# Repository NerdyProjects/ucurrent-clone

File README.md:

### ucurrent clone

This repository holds a clone of the ucurrent gold from https://www.eevblog.com/projects/ucurrent/

### Design changes
* Reimplementation of design in kicad
* exchanged switches for jumpers to reduce cost
* changed shunt usage which reduces accuracy of some measurement regions for simplicity
* used cheaper resistors for a reduced total accuracy which should be good enough for most use cases

### Description of range selection
Range selection happens by putting a jumper on the selector panel.
To change the range without powering of the device under test, just use a second jumper and remove the first one later.
The proposed sense resistors are:
* 10 milli ohms, selected in the most bottom row. (1 mV / mA)
* 90 + 10 milli ohms, selected by the second row from bottom (10 mV / mA, allows more precise measurements in the typical 0-125/250 mA region)
* 10,1 ohms (1.01 mV / µA; so 1 mV/µA with +1% error), selected by the third row from bottom. The measurement error can be mostly removed by setting a second jumper vertically on the bottom right to bridge R5.
* 10010,1 ohms (1.00101 mV / nA; so 1 mV/nA with + 0.1% error), selected by a vertical jumper on the top left)

### BOM changes
* Most precision resistors are available as 0.1% / 25ppm/K versions from the german distributor Reichelt.
* R5 has a special value of 90 mOhms and can be bridged if none can be obtained (or use a lower value).
* All shunt resistors are used as 1% versions. You are free to use more accurate ones to improve accuracy. I did rather safe 10 euros...
* The battery indication around the TPS3839 (compatible to TPS3809) is fully optional and activated by a push button. Device needs to be powered on!
* Power can be fed via an external source, power selection (external/battery/off) happens via jumper.

### BOM

| Count | Reference | Description | Purpose | Digikey | Reichelt | Price (total) |
| ---   | --------- | ----------- | ------- | ------- | -------- | ------------- |
| 1 | BT1 | CR2032 Battery Holder SMD | | 1060K-ND | | 1,05 € |
| 1 | - | Case 64x44x32mm | | | RND 455-00094 | 1,01 € |
| 2 | C1, C2 | Capacitor X7R 100 nF 0805 | blocking cap | | | 0,05 € |
| 2 | C3, C4 | Capacitor, 10 pF 0805 | opamp stabilization | | | 0,05 € |
| 2 | J2, J3, J6, J7 | Banana Jack 4mm red | measurement connections | | BIL 20 RT, BB 4 RT BD | 1,76 €, 0,64 € |
| 2 | J2, J3, J6, J7 | Banana Jack 4mm black | measurement connections | | BIL 20 SW, BB 4 SW BD | 1,76 €, 0,64 € | 
| 1 | J4 | jumper terminal, 1x03, 2,54mm | power selector | | | 0,05 € |
| 1 | J1 | jumper or screw terminal, 1x02, 2,54mm | external power | | | 0,20 € |
| 1 | J5 | double row connector, 02x04, 2,54mm | measurement range selection | | | 0,10 € |
| 4 | R1, R7, R10, R16 | Resistor 270 ohms 0805 (any) | | | | 0,05 € |
| 1 | R2 | Resistor 10 mOhms 1206 <= 1%, TC < 100 ppm | Shunt for 1mV/mA range | ERJ-6CWDR010V (0,5%, 75ppm)| | 0,75 € |
| 2 | R3, R4 | Resistor 100 kOhms 0805 (any) | voltage divider for VGND | | | 0,02 € |
| 1 | R5 | Resistor 90 mOhms 0805 <= 1%, TC < 100 ppm | Shunt for 10mV/mA range | WSL0805R0900FEA (1%, 75ppm) | | 0,85 € |
| 1 | R6 | Resistor 10 Ohms 0805 <= 1%, TC < 100 ppm | Shunt for 1mV/µA range | RR12Q10DCT-ND (0,5%, 50ppm) | | 0,13 € |
| 1 | R8 | Resistor 10 kOhms 0603 <= 1%, TC < 100 ppm | Shunt for 1mV/nA range | | SPR-0603 10,0K (0,1%, 25ppm) | 0,25 € |
| 2 | R9, R13 | Resistor 1 kOhms 0603 as precise as possible | amplifier feedback | | SPR-0603 1,00K (0,1%, 25ppm) | 0,50 € |
| 2 | R11, R14 | Resistor 6,8 kOhms 0603 as precise as possible | amplifier feedback | | SPR-0603 6,80K (0,1%, 25ppm) | 0,50 € |
| 2 | R12, R15 | Resistor 2,2 kOhms 0603 as precise as possible | amplifier feedback | | SPR-0603 2,20K (0,1%, 25ppm) | 0,50 € |
| 1 | SW1 or SW2 | Pushbutton 6mm | battery check | | RND 210-00207 | 0,12 € |
| 1 | U1 | TPS3839 | Power supply supervisor 2,65 V | TPS3839DBZ | | 0,74 € |
| 1 | U2 | LMV321 | opamp (generic) for VGND | LMV321LILT | | 0,43 € |
| 2 | U3, U4 | MAX4239AUT | ultra low offset/drift/noise opamp for measurement amplification | MAX4239AUT | | 5,30 € |
|   |        |            |                                                                  |            | | **SUM: 13,93 €** |

### Specs/Errata
Current usage of other ucurrent clone at 2.7V: 1.004 mA (via Multimeter) or 1.04 mA (via ucurrent clone @ 1mV/µA).
Unfortunately, there is a bunch of problems, which also seem to exist in the original ucurrent, but have different levels of manifestation.

* Oscillations of reference voltage: Original ucurrent gold seems to be sensitive about the exact type of U2. I tried two versions and have not been successful. Placing 100nf each over R4 and from GNDREF to V- makes GNDREF stable. This can easily be done by soldering 100nf directly above R4 and another 100nf 1206 from R13 to R4.
* Oscillations/feedback when using nA range: When operated in the nA range the output oscillates with 100kHz-1MHz. It looks like feedback is picked up in the first x10 stage and propagated to the output. Reducing bandwidth by placing 5nF from U3/pin3 (IN+) to GNDREF stops the feedback but reduces bandwidth to ~10 kHz.
* Reduced bandwidth: Output voltage drops significantly above 100 Khz.

Some scope shots, CH1 voltage over a 10 kOhm resistor, CH2 output voltage of ucurrent clone

### Case

A draft for a 3d printable case is there as well. There is some space for a 2x AAA batteryholder below the PCB but it does not contain any mounting utilities for that.

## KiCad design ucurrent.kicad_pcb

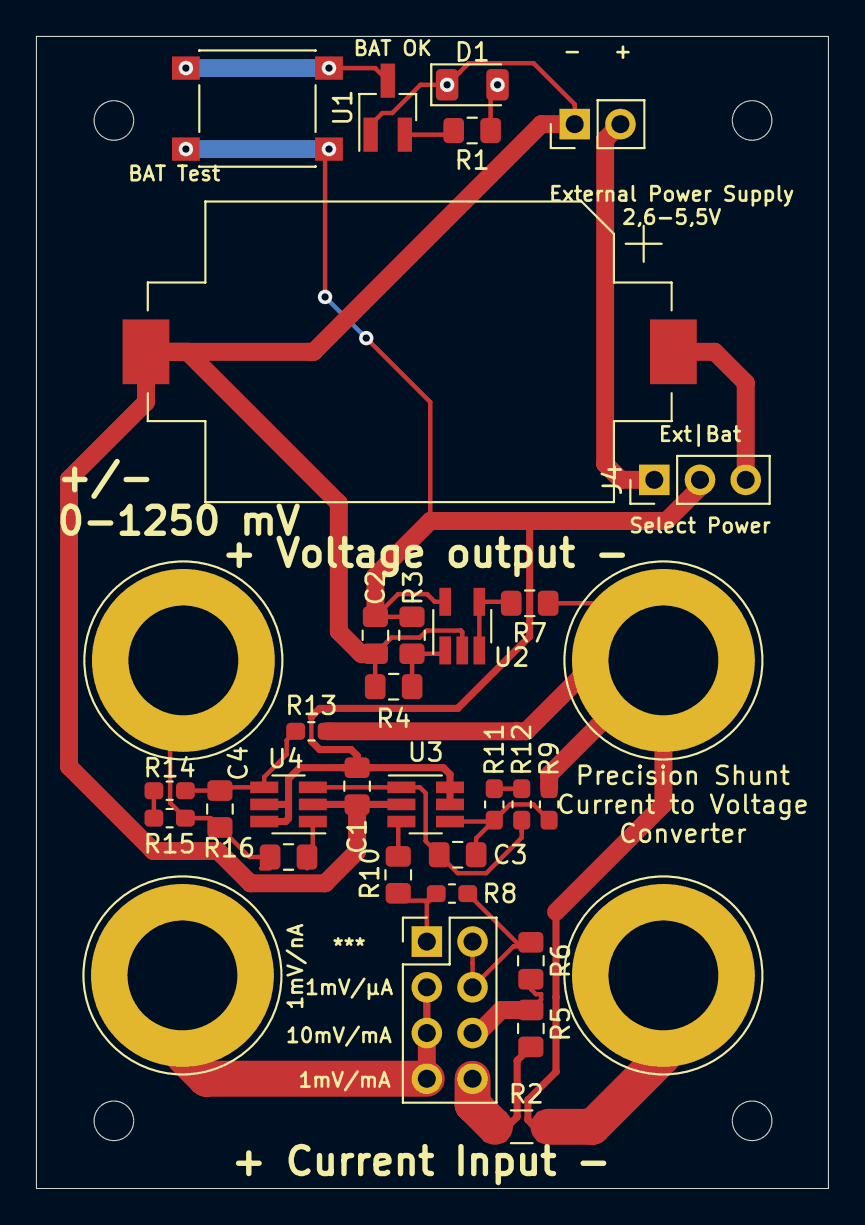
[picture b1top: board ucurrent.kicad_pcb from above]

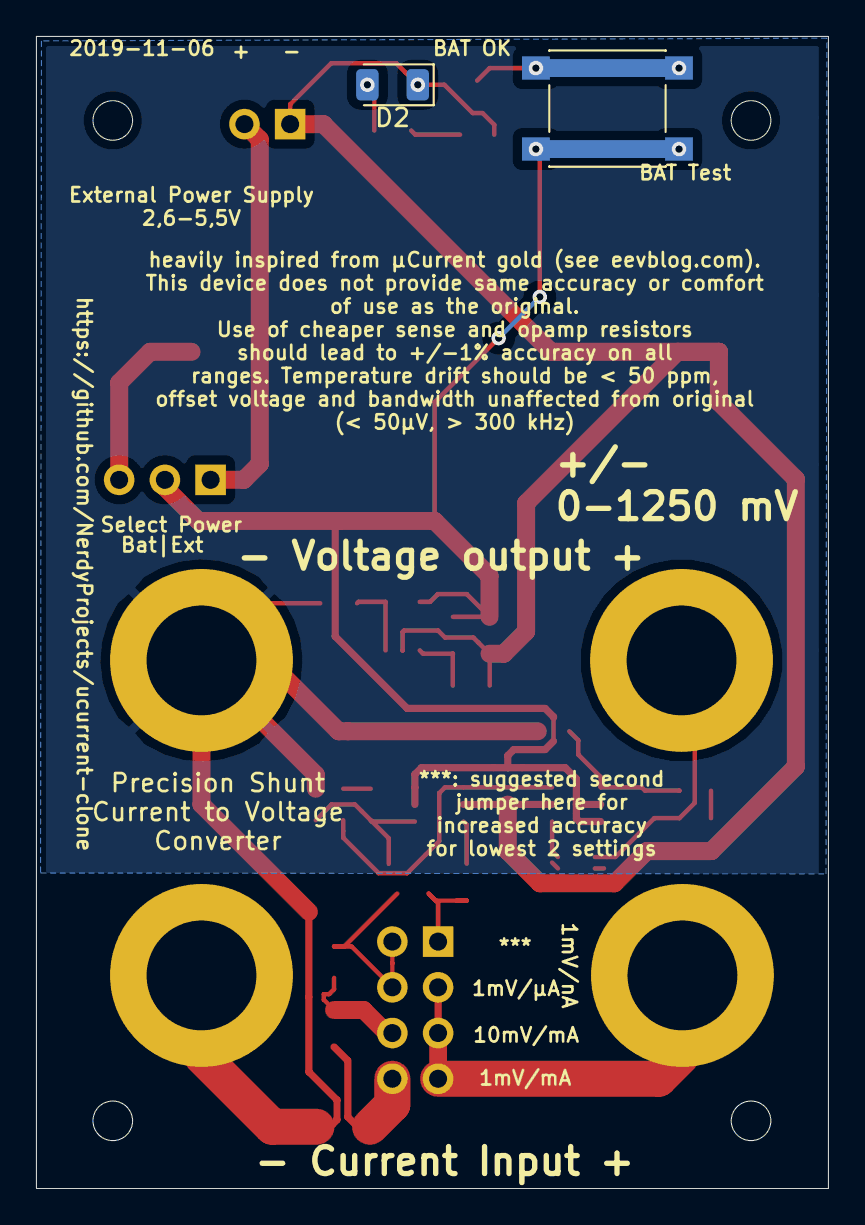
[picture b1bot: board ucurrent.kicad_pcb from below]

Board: 2 copper layers, 44.0 x 64.0 mm, 40 parts (2 on the bottom side), 23 nets.

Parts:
BT1: Battery_Cell; BatteryHolder_Keystone_1060_1x2032
C1, C2: 100n; C_0805_2012Metric_Pad1.15x1.40mm_HandSolder
C3, C4: 10pf; C_0805_2012Metric_Pad1.15x1.40mm_HandSolder
D1, D2: GREEN; LED_1206_3216Metric
H1, H2, H3, H4: MountingHole; MountingHole_2.2mm_M2
J1: Conn_01x02; PinHeader_1x02_P2.54mm_Vertical
J2: IN_P; Banana_Jack_1Pin
J3: IN_N; Banana_Jack_1Pin
J4: POWER; PinHeader_1x03_P2.54mm_Vertical
J5: Select; PinHeader_2x04_P2.54mm_Vertical
J6: OUT_P; Banana_Jack_1Pin
J7: OUT_N; Banana_Jack_1Pin
R1, R7, R10, R16: 270; R_0805_2012Metric_Pad1.15x1.40mm_HandSolder
R2: 10m 1%; R_1206_3216Metric_Pad1.42x1.75mm_HandSolder
R3, R4: 100k; R_0805_2012Metric_Pad1.15x1.40mm_HandSolder
R5: 90m 1%; R_0805_2012Metric_Pad1.15x1.40mm_HandSolder
R6: 10R 1%; R_0805_2012Metric_Pad1.15x1.40mm_HandSolder
R8: 10k 1%; R_0603_1608Metric_Pad1.05x0.95mm_HandSolder
R9, R13: 1k 0.1%; R_0603_1608Metric_Pad1.05x0.95mm_HandSolder
R11, R14: 6k8 0.1%; R_0603_1608Metric_Pad1.05x0.95mm_HandSolder
R12, R15: 2k2 0.1%; R_0603_1608Metric_Pad1.05x0.95mm_HandSolder
SW1, SW2: BAT_TEST; SW_Push_1P1T_NO_6x6mm_H9.5mm
U1: TPS3839DBZ; SOT-23_Handsoldering
U2: LMV321; SOT-23-5_HandSoldering
U3, U4: MAX4239AUT; SOT-23-6_Handsoldering

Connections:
+VDC: C1.1, C2.1, J4.2, R3.2, SW1.2, SW2.2, U2.5, U3.5, U3.6, U4.5, U4.6
-VDC: BT1.2, C1.2, C2.2, D1.1, D2.1, J1.1, R4.1, U1.1, U2.2, U3.2, U4.2
GNDREF: J3.1, J7.1, R2.2, R7.1, R9.2, R13.2
unnamed: BT1.1, J4.3
unnamed: C3.1, R12.1, U3.1, U4.3
unnamed: C3.2, R9.1, R11.2, U3.4
unnamed: C4.1, J6.1, R15.1, R16.1
unnamed: C4.2, R13.1, R14.2, U4.4
unnamed: D1.2, D2.2, R1.1
unnamed: J1.2, J4.1
unnamed: J2.1, J5.3, J5.5, J5.7
unnamed: J5.1, R8.1, R10.2
unnamed: J5.2, J5.4, R6.1, R8.2
unnamed: J5.6, R5.1, R6.2
unnamed: J5.8, R2.1, R5.2
unnamed: R1.2, U1.2
unnamed: R3.1, R4.2, U2.1
unnamed: R7.2, U2.3, U2.4
unnamed: R10.1, U3.3
unnamed: R11.1, R12.2
unnamed: R14.1, R15.2
unnamed: R16.2, U4.1
unnamed: SW1.1, SW2.1, U1.3

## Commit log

2019-11-06 ucurrent clone schematics/pcb
2019-11-06 Readme, github on silkscreen
2019-11-06 board image
2019-11-07 Allow mounting of PCB top or bottom up
2019-11-07 update part list, fix footprint
2019-11-07 update pictures
2019-11-07 link new pictures
2019-11-18 Update pcb
2019-12-19 some scope shots
2019-12-19 fix filename
2019-12-24 Case draft
